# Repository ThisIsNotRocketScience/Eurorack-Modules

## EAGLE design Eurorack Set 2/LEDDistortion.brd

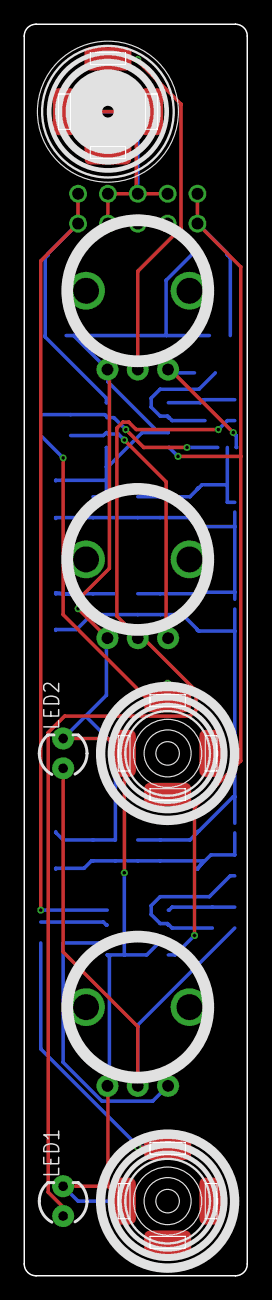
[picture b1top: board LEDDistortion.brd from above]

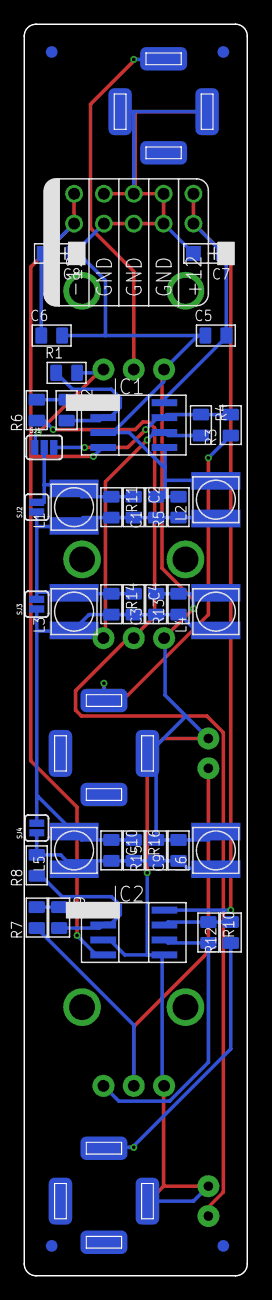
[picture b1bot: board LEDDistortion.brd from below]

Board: 2 copper layers, 19.0 x 106.5 mm, 52 parts (43 on the bottom side), 21 nets.

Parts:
C1, C2, C3, C4, C5, C6, C9, C10: 100n; C0805
C7, C8: 10u; AVX-A
GAIN1: 100k; OG-POTS_ALPS_POT_VERTICAL
IC1, IC2: TL072; SO08
L1, L2, L3, L4, L5, L6: TBD; L0420
LED1: REDBLUE; LED3MM
LED2: BLUERED; LED3MM
POST1, POST2: 100k; OG-POTS_ALPS_POT_VERTICAL
R1, R5, R8, R11, R13, R14, R15, R16: TBD; C0805
R2, R4, R9, R10: 100k; C0805
R3, R12: 100; C0805
R6, R7: 330; C0805
SJ1: SJ_3_PASTE1&2
SJ2, SJ3, SJ4: SOLDERJUMPERNC; SJ_2S
U$1: POWER_SIMPLE10; POWER_10
U$2: IN; 3.5MM-JACK-SWITCH-13MM-INPUT
U$3: OUT2; 3.5MM-JACK-SWITCH-13MM-OUTPUT
U$4: EURORACK_PCB4HP; EURORACK4HPPCB
U$5, U$7, U$8, U$9: FIDUCIAL; FIDUCIAL_1MM
U$6: OUT1; 3.5MM-JACK-SWITCH-13MM-OUTPUT

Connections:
GND: C1.2, C3.2, C5.1, C6.2, C7.-, C8.+, C9.2, GAIN1.P$1, IC1.3, IC1.5, IC2.3, IC2.5, L2.2, L4.2, L6.2, LED1.K, LED2.K, POST1.P$1, POST2.P$1, R5.2, R13.2, R15.2, U$1.3, U$1.4, U$1.5, U$1.6, U$1.7, U$1.8, U$2.RING@1, U$2.RING@2, U$2.SWITCH@1, U$2.SWITCH@2, U$3.RING@1, U$3.RING@2, U$6.RING@1, U$6.RING@2
unnamed: C2.1, L1.2, R11.1, SJ1.2, SJ2.2
unnamed: LED1.A, POST1.P$2, R6.1
unnamed: GAIN1.P$3, R1.2, SJ1.1
unnamed: IC1.6, POST1.P$3, R4.2
unnamed: R3.1, U$3.TIP@1, U$3.TIP@2
unnamed: GAIN1.P$2, U$2.TIP@1, U$2.TIP@2
unnamed: LED2.A, POST2.P$2, R7.1
unnamed: IC2.6, POST2.P$3, R10.2
unnamed: C1.1, C2.2, C4.1, L1.1, L2.1, L3.2, R5.1, R11.2, R14.1, SJ2.1, SJ3.2
unnamed: R12.1, U$6.TIP@1, U$6.TIP@2
unnamed: C9.1, C10.2, L5.1, L6.1, R8.2, R15.1, R16.2, SJ4.1
unnamed: C3.1, C4.2, C10.1, L3.1, L4.1, L5.2, R13.1, R14.2, R16.1, SJ3.1, SJ4.2
OP1NEG: IC1.2, R1.1, R2.2
OP1NEG1: IC2.2, R8.1, R9.2
OP1OUT: IC1.1, R2.1, R6.2
OP1OUT1: IC2.1, R7.2, R9.1
OP2OUT: IC1.7, R3.2, R4.1, SJ1.3
OP2OUT1: IC2.7, R10.1, R12.2
VNEG: C6.1, C8.-, IC1.4, IC2.4, U$1.1, U$1.2
VPOS: C5.2, C7.+, IC1.8, IC2.8, U$1.9, U$1.10

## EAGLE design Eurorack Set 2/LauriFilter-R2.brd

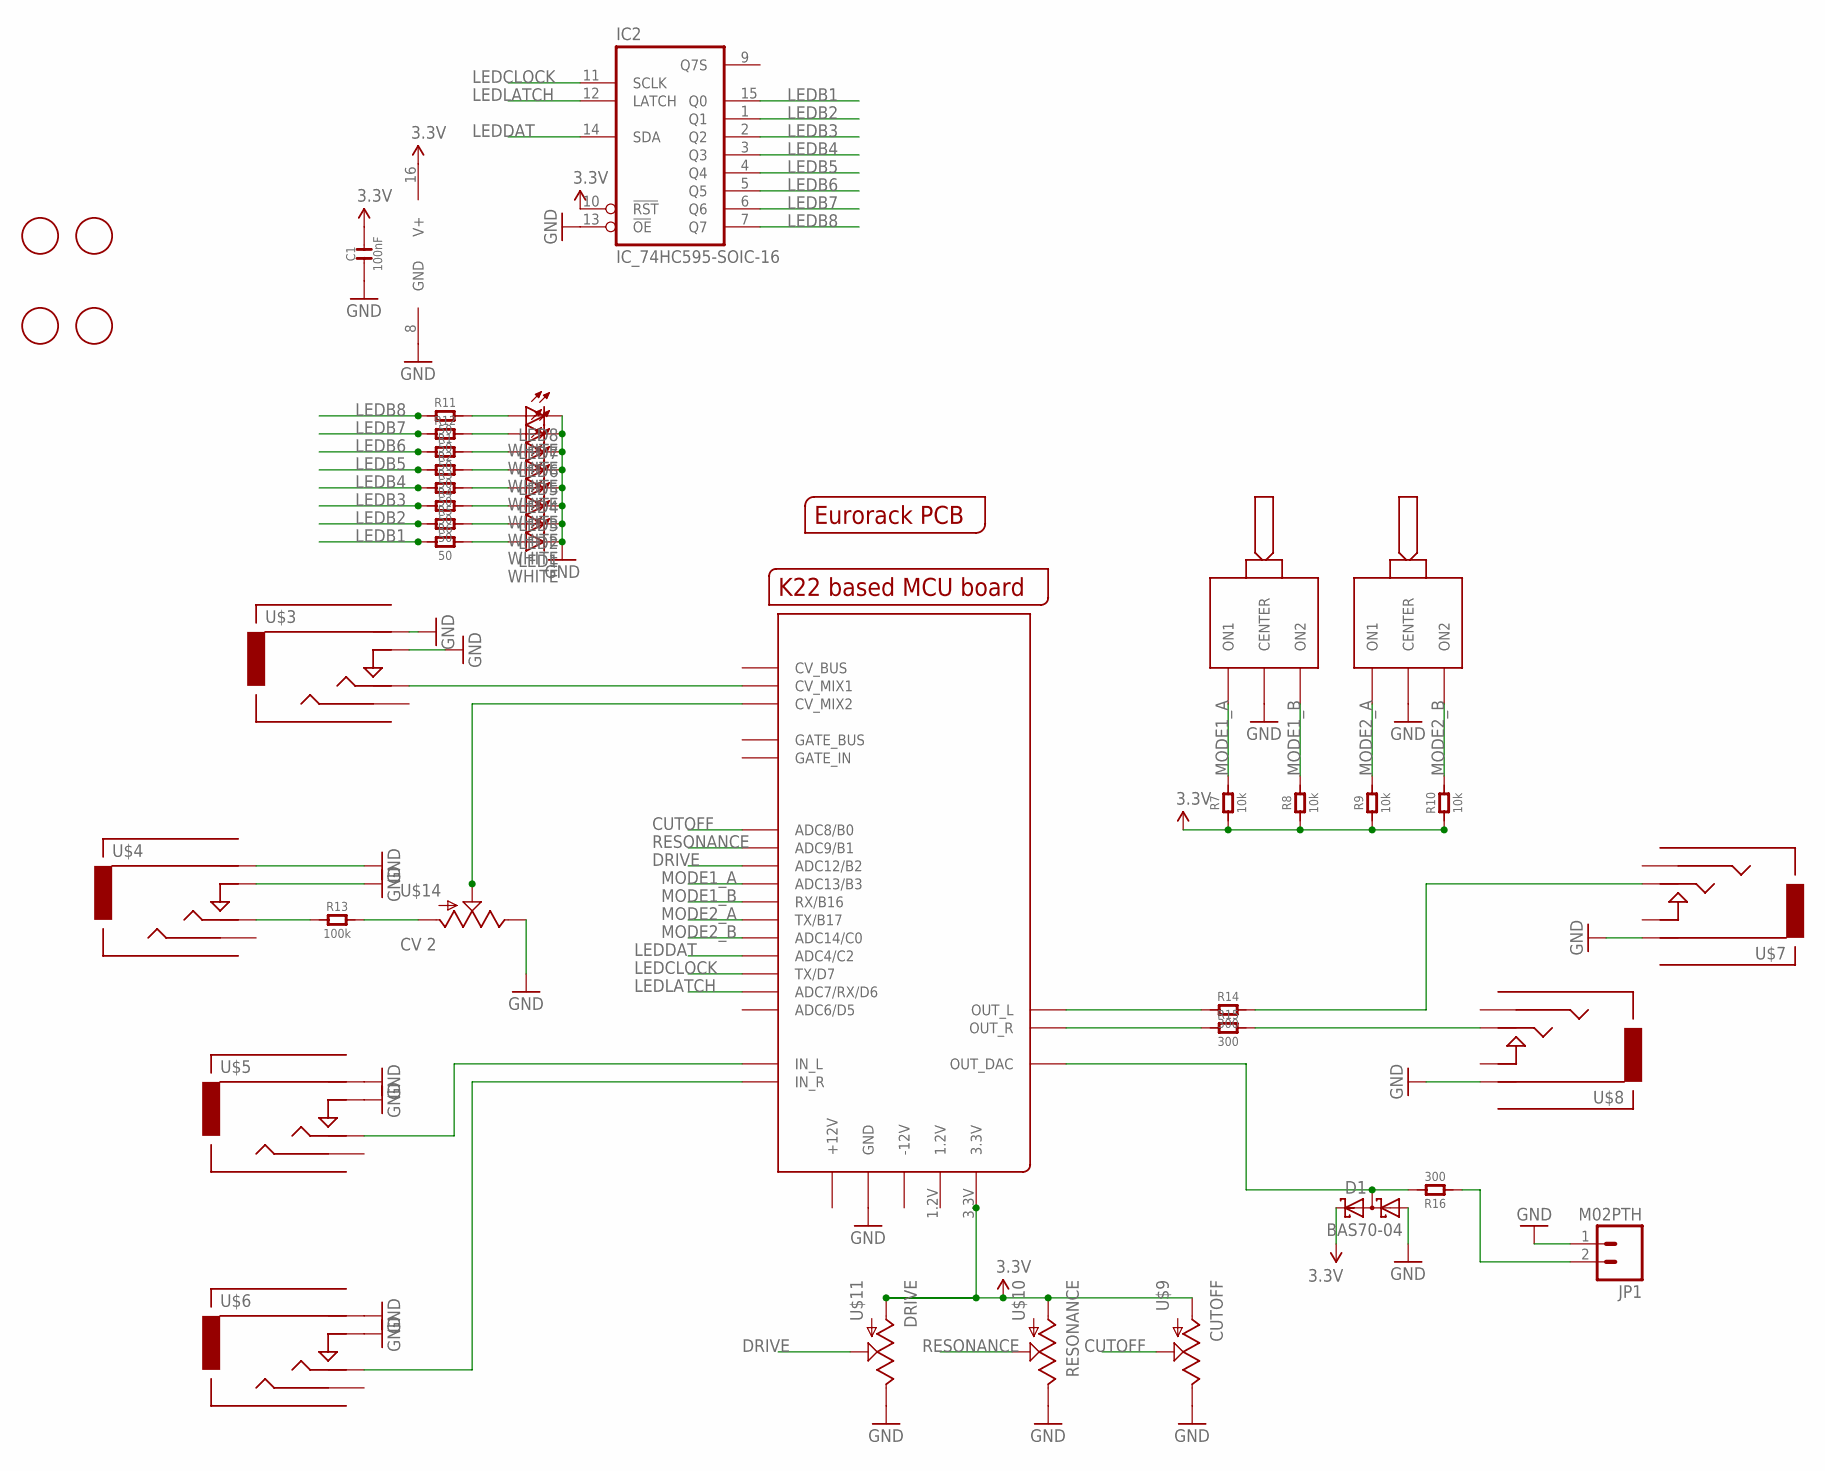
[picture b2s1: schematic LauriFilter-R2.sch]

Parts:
C1: 100nF; C0603
D1: BAS70-04; SOT23
IC2: IC_74HC595-SOIC-16; SOIC-16
JP1: M02PTH; 1X02
LED1, LED2, LED3, LED4, LED5, LED6, LED7, LED8: WHITE; LED3MM
R1, R2, R3, R4, R5, R6, R11, R12: 50; R0603
R7, R8, R9, R10: 10k; R0603
R13: 100k; R0603
R14, R15: 300; C0805
R16: 300; R0603
U$1: MCUBOARD; MCUBASEBOARD
U$2: EURORACK_PCB8HP; EURORACK8HPPCB
U$3: CV 1; 3.5MM-JACK-SWITCH-13MM-INPUT
U$4: CV 2; 3.5MM-JACK-SWITCH-13MM-INPUT
U$5: IN 1; 3.5MM-JACK-SWITCH-13MM-INPUT
U$6: IN 2; 3.5MM-JACK-SWITCH-13MM-INPUT
U$7: OUT 1; 3.5MM-JACK-SWITCH-13MM-OUTPUT
U$8: OUT 2; 3.5MM-JACK-SWITCH-13MM-OUTPUT
U$9: CUTOFF; OG-POTS_ALPS_POT_VERTICAL
U$10: RESONANCE; OG-POTS_ALPS_POT_VERTICAL
U$11: DRIVE; OG-POTS_ALPS_POT_VERTICAL
U$12, U$13: ONOFFON; MULTICOMP1MS-ONOFFON
U$14: CV 2; OG-POTS_ALPS_POT_VERTICAL
U$15, U$16, U$17, U$18: FIDUCIAL; FIDUCIAL_1MM

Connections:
3.3V: C1.2, D1.2 (C2), IC2.10 (!RST), IC2.16 (V+), R7.1, R8.1, R9.1, R10.1, U$1.3.3V, U$9.P$3 (A), U$10.P$3 (A), U$11.P$3 (A)
CUTOFF: U$1.ADC8 (ADC8/B0), U$9.P$2 (S)
DRIVE: U$1.ADC12 (ADC12/B2), U$11.P$2 (S)
GND: C1.1, D1.1 (A1), IC2.8 (GND), IC2.13 (!OE), JP1.1, LED1.K (C), LED2.K (C), LED3.K (C), LED4.K (C), LED5.K (C), LED6.K (C), LED7.K (C), LED8.K (C), U$1.GND@1 (GND), U$1.GND@2 (GND), U$1.GND@4 (GND), U$1.GND@5 (GND), U$1.GND@6 (GND), U$1.GND@7 (GND), U$1.GND@8 (GND), U$1.GND@9 (GND), U$1.GND_BUS (GND), U$3.RING@1 (RING), U$3.RING@2 (RING), U$3.SWITCH@1 (SWITCH), U$3.SWITCH@2 (SWITCH), U$4.RING@1 (RING), U$4.RING@2 (RING), U$4.SWITCH@1 (SWITCH), U$4.SWITCH@2 (SWITCH), U$5.RING@1 (RING), U$5.RING@2 (RING), U$5.SWITCH@1 (SWITCH), U$5.SWITCH@2 (SWITCH), U$6.RING@1 (RING), U$6.RING@2 (RING), U$6.SWITCH@1 (SWITCH), U$6.SWITCH@2 (SWITCH), U$7.RING@1 (RING), U$7.RING@2 (RING), U$8.RING@1 (RING), U$8.RING@2 (RING), U$9.P$1 (E), U$10.P$1 (E), U$11.P$1 (E), U$12.2 (CENTER), U$13.2 (CENTER), U$14.P$1 (E)
LEDB1: IC2.15 (Q0), R6.1
LEDB2: IC2.1 (Q1), R5.1
LEDB3: IC2.2 (Q2), R4.1
LEDB4: IC2.3 (Q3), R3.1
LEDB5: IC2.4 (Q4), R2.1
LEDB6: IC2.5 (Q5), R1.1
LEDB7: IC2.6 (Q6), R12.1
LEDB8: IC2.7 (Q7), R11.1
LEDCLOCK: IC2.11 (SCLK), U$1.TX/D7
LEDDAT: IC2.14 (SDA), U$1.ADC4 (ADC4/C2)
LEDLATCH: IC2.12 (LATCH), U$1.ADC7 (ADC7/RX/D6)
MODE1_A: R7.2, U$1.ADC13 (ADC13/B3), U$12.1 (ON1)
MODE1_B: R8.2, U$1.RX/B16, U$12.3 (ON2)
MODE2_A: R9.2, U$1.TX/B17, U$13.1 (ON1)
MODE2_B: R10.2, U$1.ADC14 (ADC14/C0), U$13.3 (ON2)
unnamed: U$1.IN_L, U$5.TIP@1 (TIP), U$5.TIP@2 (TIP)
unnamed: U$1.IN_R, U$6.TIP@1 (TIP), U$6.TIP@2 (TIP)
unnamed: U$1.CV_MIX1, U$3.TIP@1 (TIP), U$3.TIP@2 (TIP)
unnamed: U$1.CV_MIX2, U$14.P$2 (S)
unnamed: R14.2, U$7.TIP@1 (TIP), U$7.TIP@2 (TIP)
unnamed: R15.2, U$8.TIP@1 (TIP), U$8.TIP@2 (TIP)
unnamed: LED1.A, R6.2
unnamed: LED2.A, R5.2
unnamed: R14.1, U$1.OUT_L
unnamed: R15.1, U$1.OUT_R
unnamed: D1.3 (C1A2), R16.2, U$1.OUT_DAC
unnamed: LED3.A, R4.2
unnamed: LED4.A, R3.2
unnamed: LED5.A, R2.2
unnamed: LED6.A, R1.2
unnamed: LED7.A, R12.2
unnamed: LED8.A, R11.2
unnamed: JP1.2, R16.1
RESONANCE: U$1.ADC9 (ADC9/B1), U$10.P$2 (S)

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
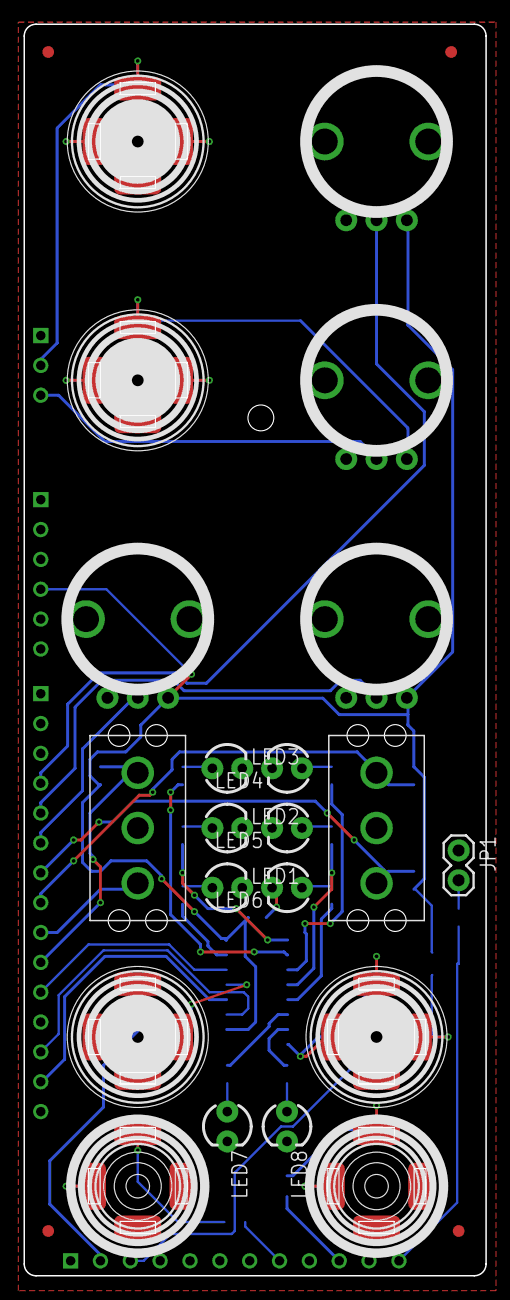
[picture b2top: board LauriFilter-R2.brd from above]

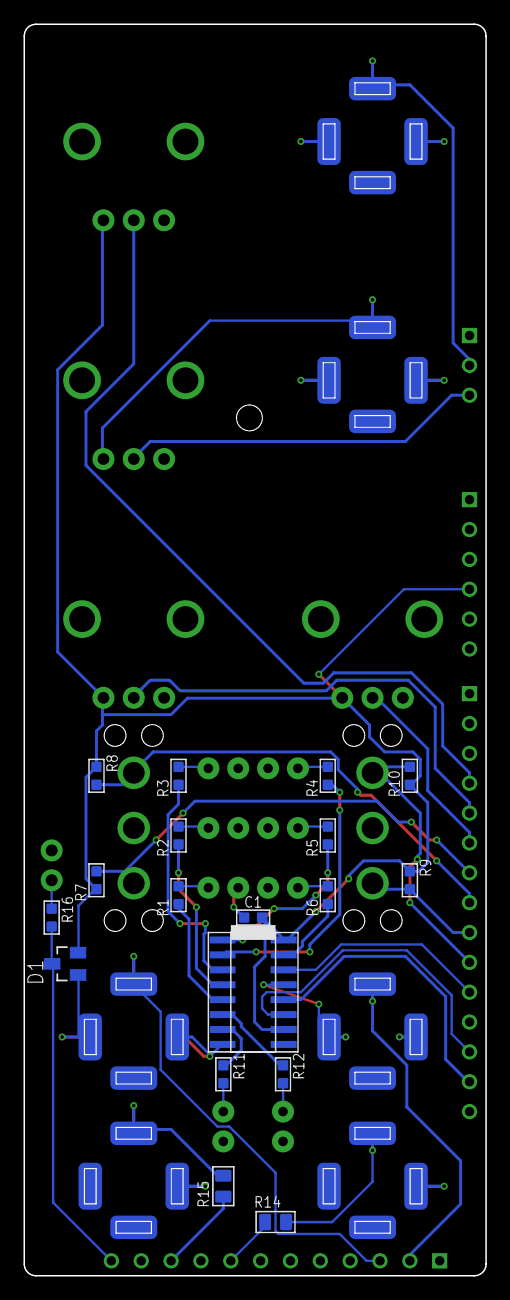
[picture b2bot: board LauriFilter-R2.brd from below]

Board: 2 copper layers, 39.3 x 106.5 mm, 45 parts (18 on the bottom side), 39 nets.

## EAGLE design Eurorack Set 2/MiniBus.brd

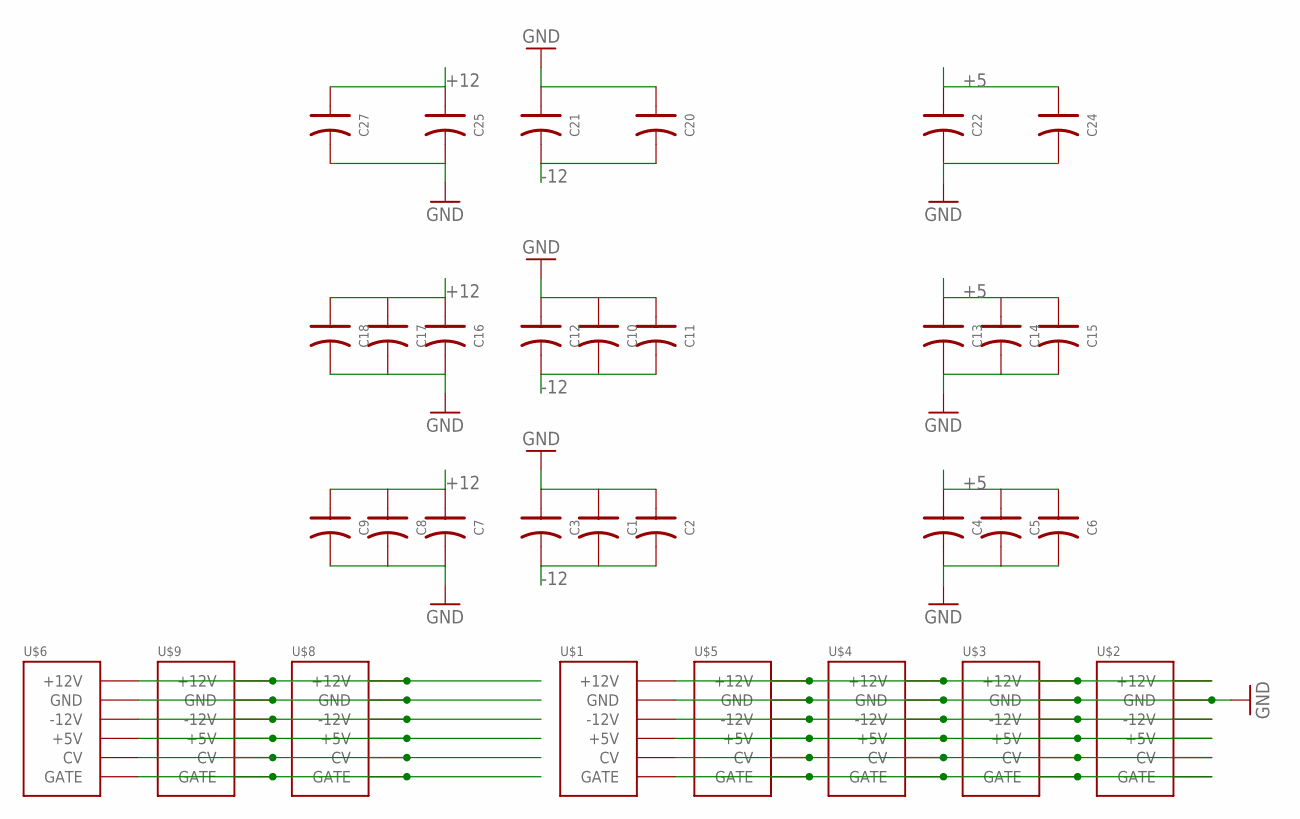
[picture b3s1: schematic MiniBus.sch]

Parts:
C1, C2, C3, C4, C5, C6, C7, C8, C9, C10, C11, C12, C13, C14, C15, C16, C17, C18, C20, C21, C22, C24, C25, C27: C-POLAR-A; AVX-A
U$1, U$2, U$3, U$4, U$5, U$6, U$8, U$9: POWER; POWER_16

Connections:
+5: C4.+ (1), C5.+ (1), C6.+ (1), C13.+ (1), C14.+ (1), C15.+ (1), C22.+ (1), C24.+ (1), U$1.11 (+5V), U$1.12 (+5V), U$2.11 (+5V), U$2.12 (+5V), U$3.11 (+5V), U$3.12 (+5V), U$4.11 (+5V), U$4.12 (+5V), U$5.11 (+5V), U$5.12 (+5V), U$6.11 (+5V), U$6.12 (+5V), U$8.11 (+5V), U$8.12 (+5V), U$9.11 (+5V), U$9.12 (+5V)
+12: C7.+ (1), C8.+ (1), C9.+ (1), C16.+ (1), C17.+ (1), C18.+ (1), C25.+ (1), C27.+ (1), U$1.9 (+12V), U$1.10 (+12V), U$2.9 (+12V), U$2.10 (+12V), U$3.9 (+12V), U$3.10 (+12V), U$4.9 (+12V), U$4.10 (+12V), U$5.9 (+12V), U$5.10 (+12V), U$6.9 (+12V), U$6.10 (+12V), U$8.9 (+12V), U$8.10 (+12V), U$9.9 (+12V), U$9.10 (+12V)
-12: C1.- (2), C2.- (2), C3.- (2), C10.- (2), C11.- (2), C12.- (2), C20.- (2), C21.- (2), U$1.1 (-12V), U$1.2 (-12V), U$2.1 (-12V), U$2.2 (-12V), U$3.1 (-12V), U$3.2 (-12V), U$4.1 (-12V), U$4.2 (-12V), U$5.1 (-12V), U$5.2 (-12V), U$6.1 (-12V), U$6.2 (-12V), U$8.1 (-12V), U$8.2 (-12V), U$9.1 (-12V), U$9.2 (-12V)
CV: U$1.13 (CV), U$1.14 (CV), U$2.13 (CV), U$2.14 (CV), U$3.13 (CV), U$3.14 (CV), U$4.13 (CV), U$4.14 (CV), U$5.13 (CV), U$5.14 (CV), U$6.13 (CV), U$6.14 (CV), U$8.13 (CV), U$8.14 (CV), U$9.13 (CV), U$9.14 (CV)
GATE: U$1.15 (GATE), U$1.16 (GATE), U$2.15 (GATE), U$2.16 (GATE), U$3.15 (GATE), U$3.16 (GATE), U$4.15 (GATE), U$4.16 (GATE), U$5.15 (GATE), U$5.16 (GATE), U$6.15 (GATE), U$6.16 (GATE), U$8.15 (GATE), U$8.16 (GATE), U$9.15 (GATE), U$9.16 (GATE)
GND: C1.+ (1), C2.+ (1), C3.+ (1), C4.- (2), C5.- (2), C6.- (2), C7.- (2), C8.- (2), C9.- (2), C10.+ (1), C11.+ (1), C12.+ (1), C13.- (2), C14.- (2), C15.- (2), C16.- (2), C17.- (2), C18.- (2), C20.+ (1), C21.+ (1), C22.- (2), C24.- (2), C25.- (2), C27.- (2), U$1.3 (GND), U$1.4 (GND), U$1.5 (GND), U$1.6 (GND), U$1.7 (GND), U$1.8 (GND), U$2.3 (GND), U$2.4 (GND), U$2.5 (GND), U$2.6 (GND), U$2.7 (GND), U$2.8 (GND), U$3.3 (GND), U$3.4 (GND), U$3.5 (GND), U$3.6 (GND), U$3.7 (GND), U$3.8 (GND), U$4.3 (GND), U$4.4 (GND), U$4.5 (GND), U$4.6 (GND), U$4.7 (GND), U$4.8 (GND), U$5.3 (GND), U$5.4 (GND), U$5.5 (GND), U$5.6 (GND), U$5.7 (GND), U$5.8 (GND), U$6.3 (GND), U$6.4 (GND), U$6.5 (GND), U$6.6 (GND), U$6.7 (GND), U$6.8 (GND), U$8.3 (GND), U$8.4 (GND), U$8.5 (GND), U$8.6 (GND), U$8.7 (GND), U$8.8 (GND), U$9.3 (GND), U$9.4 (GND), U$9.5 (GND), U$9.6 (GND), U$9.7 (GND), U$9.8 (GND)

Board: 2 copper layers, 32 parts (9 on the bottom side), 6 nets, no tracks yet.

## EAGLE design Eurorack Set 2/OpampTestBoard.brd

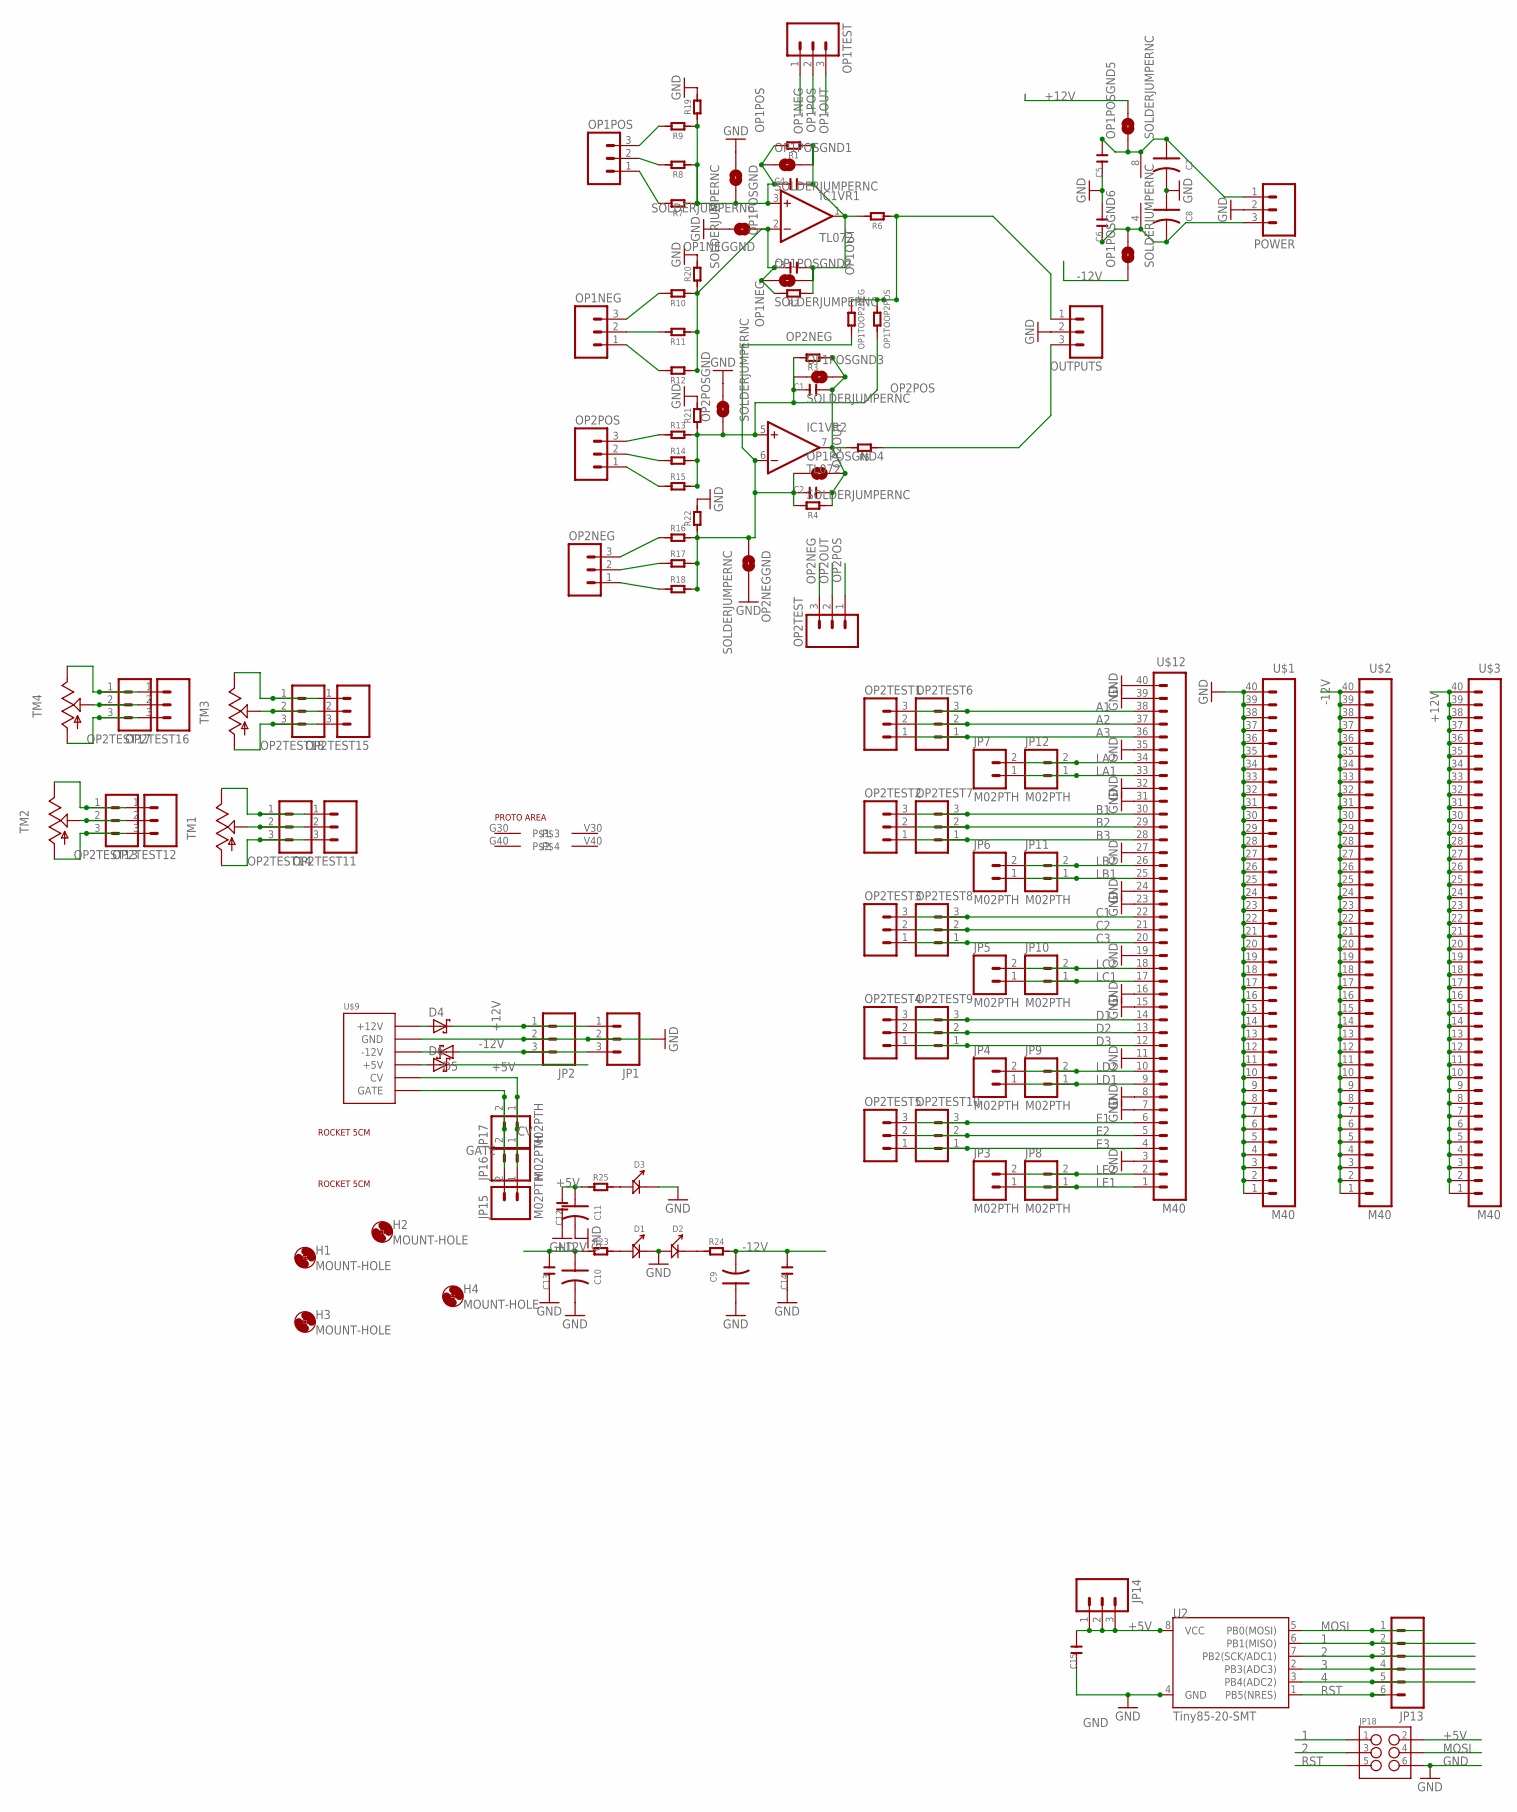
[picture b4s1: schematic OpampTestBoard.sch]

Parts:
C1, C2, C3, C4, C5, C6, C12, C13, C14: C-0805; C0805
C7, C8, C9, C10, C11: C-POLAR-A; AVX-A
C15: C-0603; C0603
D1, D2, D3: LED; LED0603
D4, D5, D6: SCHOTTKY-DIODEDO41; DO41-10
H1, H2, H3, H4: MOUNT-HOLE; 3.2-NOMARKINGS-SMALLSAFEZONE
IC1: TL072; SO08
JP1, JP2, JP14: M03PTH; 1X03
JP3, JP4, JP5, JP6, JP7, JP8, JP9, JP10, JP11, JP12, JP15, JP16, JP17: M02PTH; 1X02
JP13: M06SIP; 1X06
JP18: M03X2SMT; 2X3_SMT_POSTS
OP1NEG, OP1POS, OP1TEST, OP2NEG, OP2POS, OP2TEST, OP2TEST1, OP2TEST2, OP2TEST3, OP2TEST4, OP2TEST5, OP2TEST6, OP2TEST7, OP2TEST8, OP2TEST9, OP2TEST10, OP2TEST11, OP2TEST12, OP2TEST13, OP2TEST14, OP2TEST15, OP2TEST16, OP2TEST17, OP2TEST18: M03PTH; 1X03
OP1NEGGND, OP1POSGND, OP1POSGND1, OP1POSGND2, OP1POSGND3, OP1POSGND4, OP1POSGND5, OP1POSGND6, OP2NEGGND, OP2POSGND: SOLDERJUMPERNC; SJ_2S
OP1TOOP2NEG, OP1TOOP2POS: R-0603; R0603
OUTPUTS: M03PTH; 1X03
POWER: M03PTH; 1X03
R1, R2, R3, R4, R5, R6, R7, R8, R9, R10, R11, R12, R13, R14, R15, R16, R17, R18, R19, R20, R21, R22, R23, R24, R25: R-0603; R0603
TM1, TM2, TM3, TM4: TRIM; 6MM
U2: Tiny85-20-SMT; SO08-EIAJ
U$1, U$2, U$3, U$12: M40; 1X40
U$9: POWER; POWER_16
U$10, U$17: ROCKET-5CM
U$32: PROTOAREA; PROTO_10_24

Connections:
1: JP13.2, JP18.1, U2.6 (PB1(MISO))
2: JP13.3, JP18.3, U2.7 (PB2(SCK/ADC1))
3: JP13.4, U2.2 (PB3(ADC3))
4: JP13.5, U2.3 (PB4(ADC2))
+5V: C11.+ (1), C12.2, C15.2, D6.C, JP14.1, JP14.2, JP14.3, JP18.2, R25.1, U2.8 (VCC)
+12V: C10.+ (1), C13.2, D4.C, JP1.1, JP2.1, OP1POSGND5.2, R23.1, U$3.1, U$3.2, U$3.3, U$3.4, U$3.5, U$3.6, U$3.7, U$3.8, U$3.9, U$3.10, U$3.11, U$3.12, U$3.13, U$3.14, U$3.15, U$3.16, U$3.17, U$3.18, U$3.19, U$3.20, U$3.21, U$3.22, U$3.23, U$3.24, U$3.25, U$3.26, U$3.27, U$3.28, U$3.29, U$3.30, U$3.31, U$3.32, U$3.33, U$3.34, U$3.35, U$3.36, U$3.37, U$3.38, U$3.39, U$3.40
-12V: C9.- (2), C14.2, D5.A, JP1.3, JP2.3, OP1POSGND6.1, R24.2, U$2.1, U$2.2, U$2.3, U$2.4, U$2.5, U$2.6, U$2.7, U$2.8, U$2.9, U$2.10, U$2.11, U$2.12, U$2.13, U$2.14, U$2.15, U$2.16, U$2.17, U$2.18, U$2.19, U$2.20, U$2.21, U$2.22, U$2.23, U$2.24, U$2.25, U$2.26, U$2.27, U$2.28, U$2.29, U$2.30, U$2.31, U$2.32, U$2.33, U$2.34, U$2.35, U$2.36, U$2.37, U$2.38, U$2.39, U$2.40
A1: OP2TEST1.3, OP2TEST6.3, U$12.38
A2: OP2TEST1.2, OP2TEST6.2, U$12.37
A3: OP2TEST1.1, OP2TEST6.1, U$12.36
B1: OP2TEST2.3, OP2TEST7.3, U$12.30
B2: OP2TEST2.2, OP2TEST7.2, U$12.29
B3: OP2TEST2.1, OP2TEST7.1, U$12.28
C1: OP2TEST3.3, OP2TEST8.3, U$12.22
C2: OP2TEST3.2, OP2TEST8.2, U$12.21
C3: OP2TEST3.1, OP2TEST8.1, U$12.20
CV: JP15.1, JP16.1, JP17.1, U$9.13 (CV), U$9.14 (CV)
D1: OP2TEST4.3, OP2TEST9.3, U$12.14
D2: OP2TEST4.2, OP2TEST9.2, U$12.13
D3: OP2TEST4.1, OP2TEST9.1, U$12.12
E1: OP2TEST5.3, OP2TEST10.3, U$12.6
E2: OP2TEST5.2, OP2TEST10.2, U$12.5
E3: OP2TEST5.1, OP2TEST10.1, U$12.4
GATE: JP15.2, JP16.2, JP17.2, U$9.15 (GATE), U$9.16 (GATE)
GND: C5.1, C6.2, C7.- (2), C8.+ (1), C9.+ (1), C10.- (2), C11.- (2), C12.1, C13.1, C14.1, C15.1, D1.-, D2.+, D3.-, JP1.2, JP2.2, JP18.6, OP1NEGGND.2, OP1POSGND.1, OP2NEGGND.2, OP2POSGND.2, OUTPUTS.2, POWER.2, R19.2, R20.2, R21.2, R22.2, U2.4 (GND), U$1.1, U$1.2, U$1.3, U$1.4, U$1.5, U$1.6, U$1.7, U$1.8, U$1.9, U$1.10, U$1.11, U$1.12, U$1.13, U$1.14, U$1.15, U$1.16, U$1.17, U$1.18, U$1.19, U$1.20, U$1.21, U$1.22, U$1.23, U$1.24, U$1.25, U$1.26, U$1.27, U$1.28, U$1.29, U$1.30, U$1.31, U$1.32, U$1.33, U$1.34, U$1.35, U$1.36, U$1.37, U$1.38, U$1.39, U$1.40, U$9.3 (GND), U$9.4 (GND), U$9.5 (GND), U$9.6 (GND), U$9.7 (GND), U$9.8 (GND), U$12.3, U$12.7, U$12.8, U$12.11, U$12.15, U$12.16, U$12.19, U$12.23, U$12.24, U$12.27, U$12.31, U$12.32, U$12.35, U$12.39, U$12.40
LA1: JP7.1, JP12.1, U$12.33
LA2: JP7.2, JP12.2, U$12.34
LB1: JP6.1, JP11.1, U$12.25
LB2: JP6.2, JP11.2, U$12.26
LC1: JP5.1, JP10.1, U$12.17
LC2: JP5.2, JP10.2, U$12.18
LD1: JP4.1, JP9.1, U$12.9
LD2: JP4.2, JP9.2, U$12.10
LE1: JP3.1, JP8.1, U$12.1
LE2: JP3.2, JP8.2, U$12.2
MOSI: JP13.1, JP18.4, U2.5 (PB0(MOSI))
unnamed: OP1POS.3, R9.2
unnamed: OP1TOOP2NEG.1, OP1TOOP2POS.1, OUTPUTS.1, R6.1
unnamed: OP1POS.2, R8.2
unnamed: OUTPUTS.3, R5.1
unnamed: OP2TEST11.2, OP2TEST14.2, TM1.S
unnamed: OP2TEST12.2, OP2TEST13.2, TM2.S
unnamed: OP1POS.1, R7.2
unnamed: OP1NEG.3, R10.2
unnamed: OP1NEG.2, R11.2
unnamed: OP1NEG.1, R12.2
unnamed: OP2POS.3, R13.1
unnamed: OP2POS.2, R14.1
unnamed: OP2POS.1, R15.1
unnamed: OP2NEG.3, R16.1
unnamed: OP2NEG.2, R17.1
unnamed: OP2NEG.1, R18.1
unnamed: OP2TEST12.1, OP2TEST13.1, TM2.E
unnamed: D3.+, R25.2
unnamed: D1.+, R23.2
unnamed: D2.-, R24.1
unnamed: OP2TEST12.3, OP2TEST13.3, TM2.A
unnamed: OP2TEST11.1, OP2TEST14.1, TM1.E
unnamed: OP2TEST11.3, OP2TEST14.3, TM1.A
unnamed: OP2TEST15.2, OP2TEST18.2, TM3.S
unnamed: OP2TEST16.2, OP2TEST17.2, TM4.S
unnamed: OP2TEST16.1, OP2TEST17.1, TM4.E
unnamed: OP2TEST16.3, OP2TEST17.3, TM4.A
unnamed: OP2TEST15.1, OP2TEST18.1, TM3.E
unnamed: OP2TEST15.3, OP2TEST18.3, TM3.A
unnamed: D4.A, U$9.9 (+12V), U$9.10 (+12V)
unnamed: D5.C, U$9.1 (-12V), U$9.2 (-12V)
unnamed: D6.A, U$9.11 (+5V), U$9.12 (+5V)
OP1NEG: C3.1, IC1.2 (-IN), OP1NEGGND.1, OP1POSGND2.1, OP1TEST.1, R2.2, R10.1, R11.1, R12.1, R20.1
OP1OUT: C3.2, C4.2, IC1.1 (OUT), OP1POSGND1.2, OP1POSGND2.2, OP1TEST.3, R1.1, R2.1, R6.2
OP1POS: C4.1, IC1.3 (+IN), OP1POSGND.2, OP1POSGND1.1, OP1TEST.2, R1.2, R7.1, R8.1, R9.1, R19.1
OP2NEG: C2.1, IC1.6 (-IN), OP1POSGND4.1, OP1TOOP2NEG.2, OP2NEGGND.1, OP2TEST.3, R4.2, R16.2, R17.2, R18.2, R22.1
OP2OUT: C1.2, C2.2, IC1.7 (OUT), OP1POSGND3.2, OP1POSGND4.2, OP2TEST.2, R3.1, R4.1, R5.2
OP2POS: C1.1, IC1.5 (+IN), OP1POSGND3.1, OP1TOOP2POS.2, OP2POSGND.1, OP2TEST.1, R3.2, R13.2, R14.2, R15.2, R21.1
RST: JP13.6, JP18.5, U2.1 (PB5(NRES))
VNEG: C6.1, C8.- (2), IC1.4 (V-), OP1POSGND6.2, POWER.3
VPOS: C5.2, C7.+ (1), IC1.8 (V+), OP1POSGND5.1, POWER.1

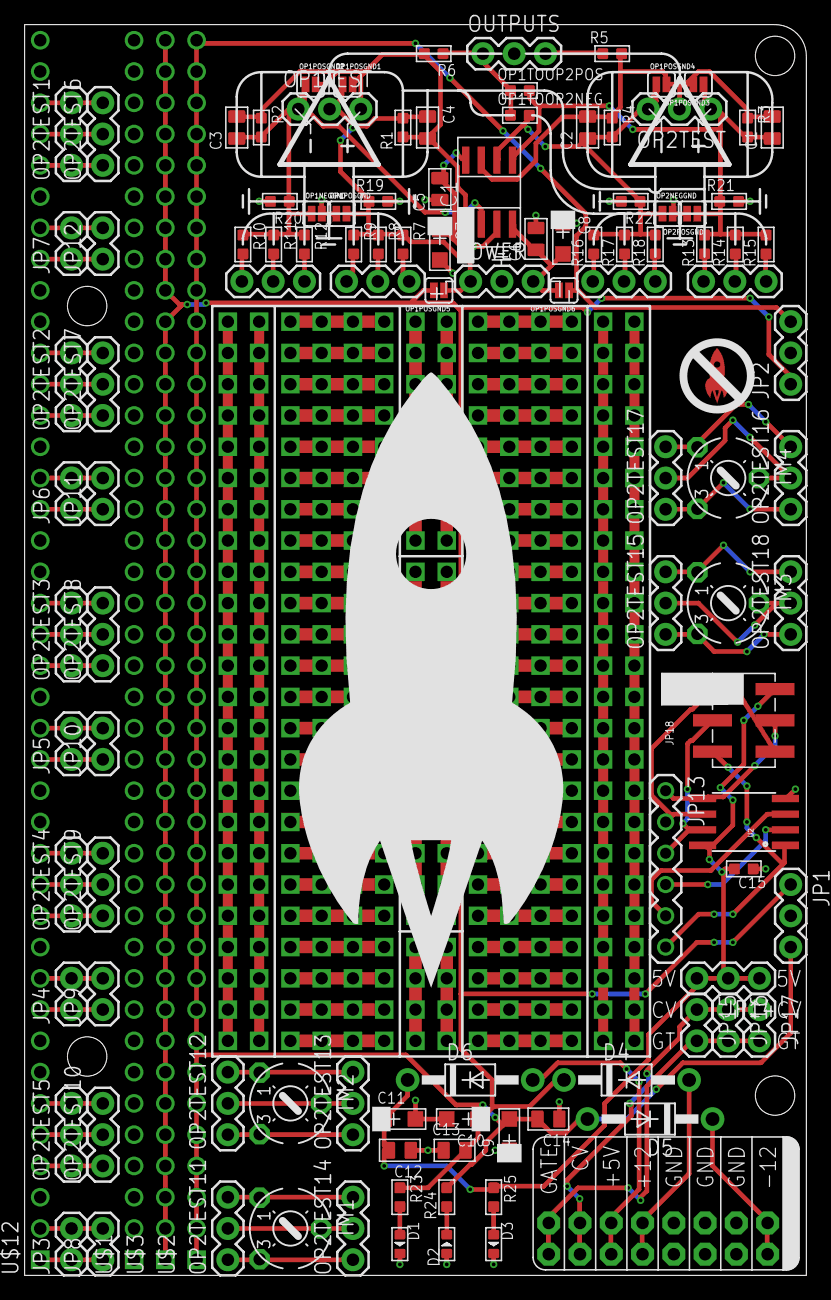
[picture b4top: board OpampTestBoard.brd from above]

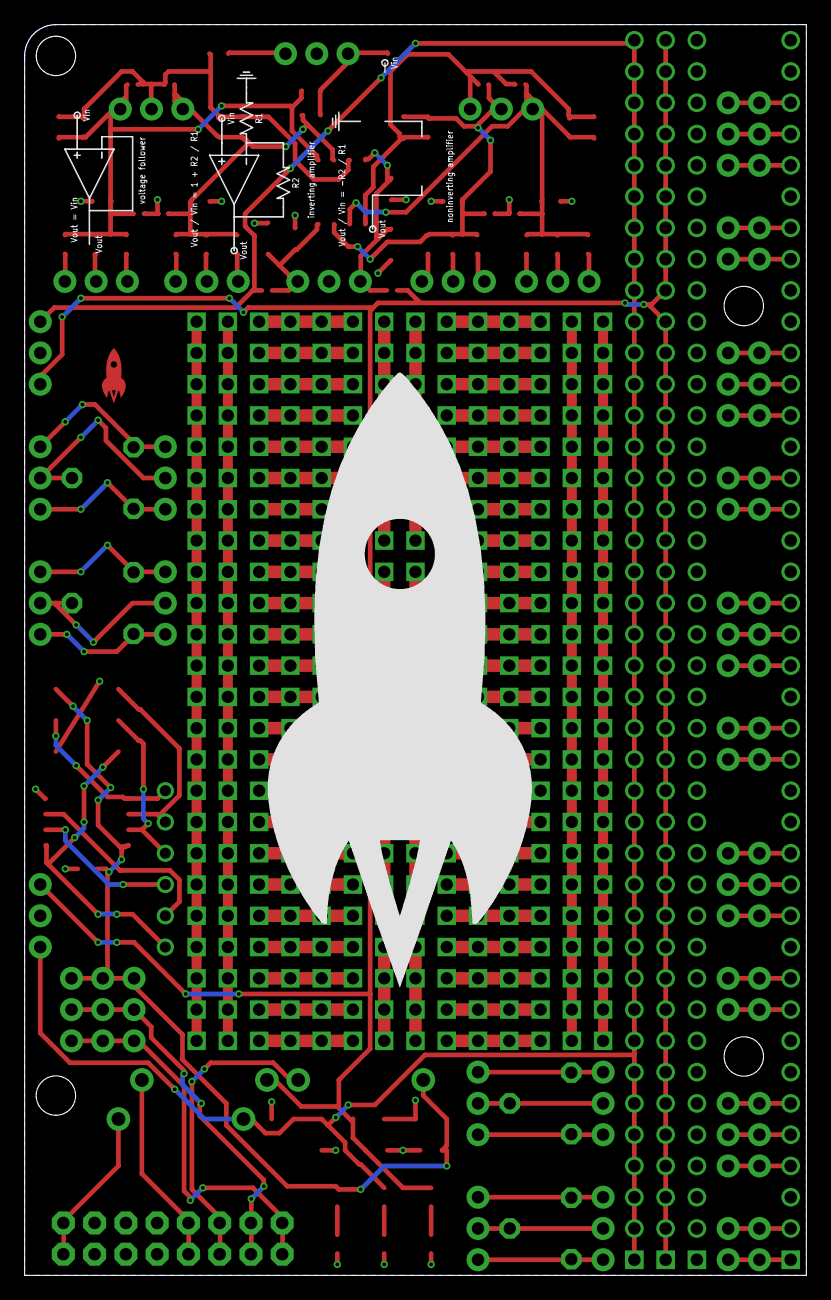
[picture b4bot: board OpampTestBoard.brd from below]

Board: 2 copper layers, 63.5 x 101.6 mm, 125 parts (5 on the bottom side), 77 nets.

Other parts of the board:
U$4, U$7: SYMBOLSOPAMP; SYMB_OPAMP
U$5: R2; RESISTOR
U$6: R1; RESISTOR
U$8: SMALLROCKET

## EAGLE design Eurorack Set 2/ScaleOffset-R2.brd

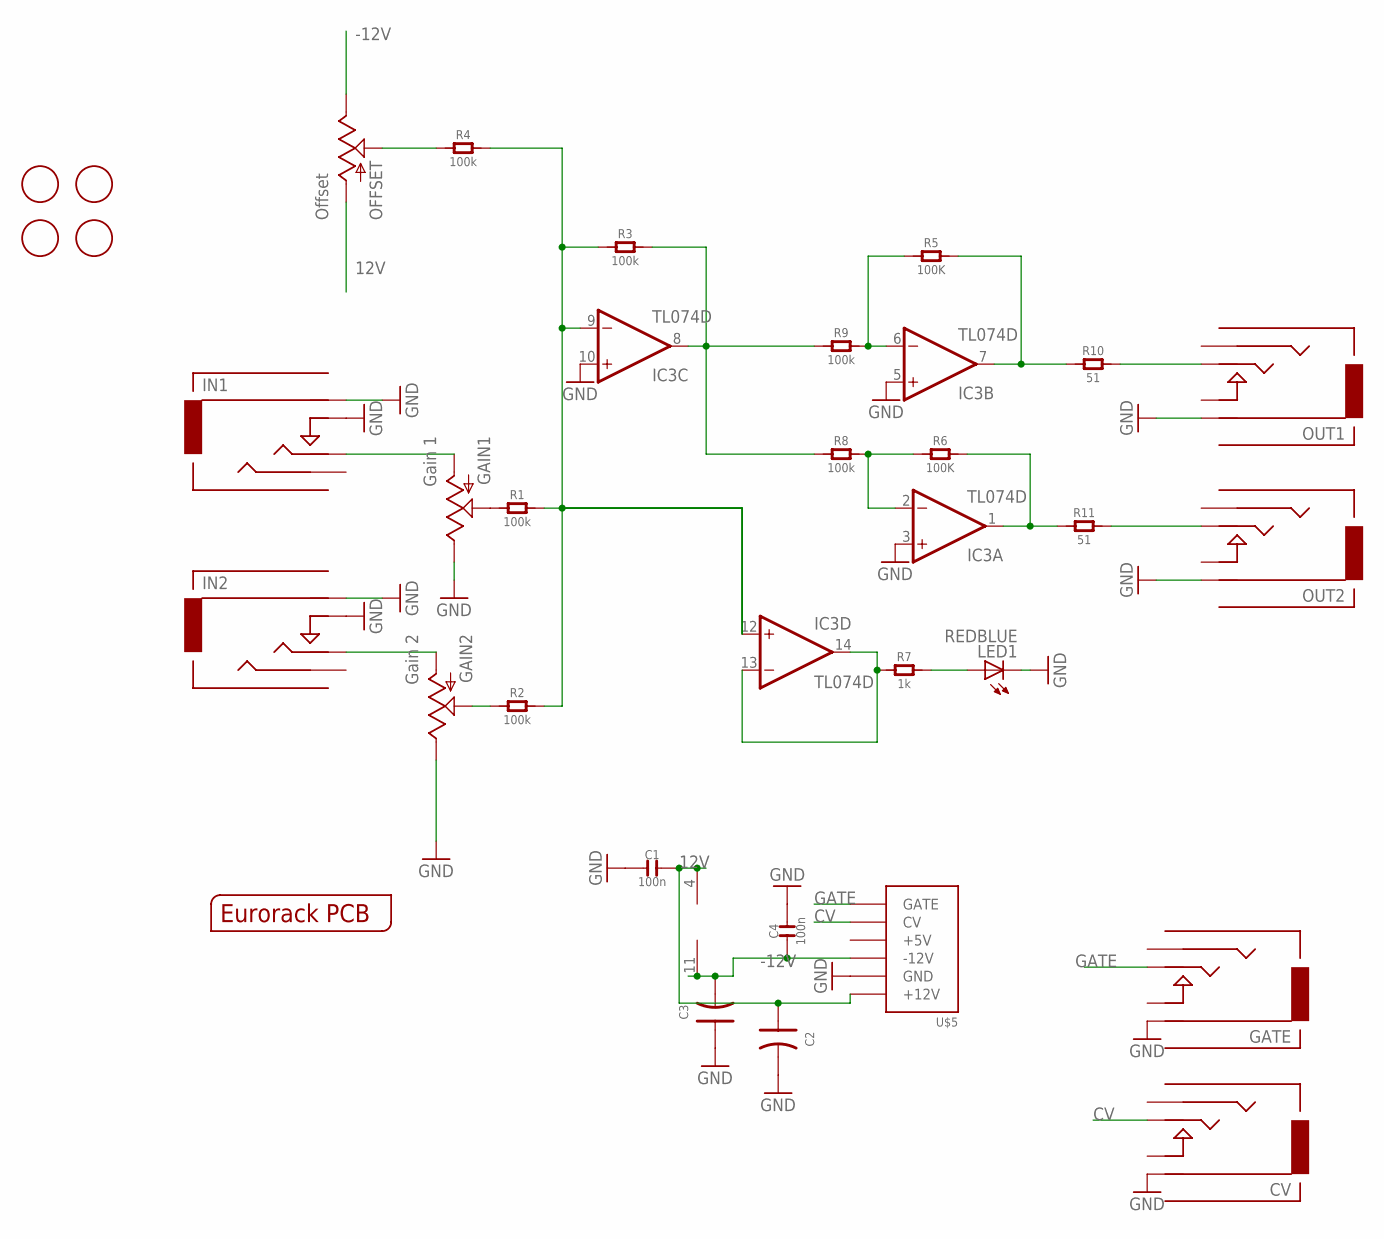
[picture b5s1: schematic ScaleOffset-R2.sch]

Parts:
C1, C4: 100n; C0603
C2, C3: C-POLAR-A; AVX-A
CV: CV; 3.5MM-JACK-SWITCH-13MM-OUTPUT
GAIN1: Gain 1; OG-POTS_ALPS_POT_VERTICAL
GAIN2: Gain 2; OG-POTS_ALPS_POT_VERTICAL
GATE: GATE; 3.5MM-JACK-SWITCH-13MM-OUTPUT
IC3: TL074D; SO14
IN1: Input 1; 3.5MM-JACK-SWITCH-13MM-INPUT
IN2: Input 2; 3.5MM-JACK-SWITCH-13MM-INPUT
LED1: REDBLUE; LED3MM
OFFSET: Offset; OG-POTS_ALPS_POT_VERTICAL
OUT1: 2; 3.5MM-JACK-SWITCH-13MM-OUTPUT
OUT2: 1; 3.5MM-JACK-SWITCH-13MM-OUTPUT
R1, R2, R3, R4, R8, R9: 100k; R0603
R5, R6: 100K; R0603
R7: 1k; R0603
R10, R11: 51; C0805
U$1, U$2, U$3, U$4: FIDUCIAL; FIDUCIAL_1MM
U$5: POWER; POWER_16
U$12: EURORACK_PCB6HP; EURORACK6HPPCB

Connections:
12V: C1.2, C2.+ (1), IC3.4 (V+), OFFSET.P$3 (A), U$5.9 (+12V), U$5.10 (+12V)
-12V: C3.- (2), C4.1, IC3.11 (V-), OFFSET.P$1 (E), U$5.1 (-12V), U$5.2 (-12V)
CV: CV.TIP@1 (TIP), CV.TIP@2 (TIP), U$5.13 (CV), U$5.14 (CV)
FBOUT1: IC3.7 (OUT), R5.2, R10.1
FBOUT2: IC3.1 (OUT), R6.2, R11.1
GATE: GATE.TIP@1 (TIP), GATE.TIP@2 (TIP), U$5.15 (GATE), U$5.16 (GATE)
GND: C1.1, C2.- (2), C3.+ (1), C4.2, CV.RING@1 (RING), CV.RING@2 (RING), GAIN1.P$1 (E), GAIN2.P$1 (E), GATE.RING@1 (RING), GATE.RING@2 (RING), IC3.3 (+IN), IC3.5 (+IN), IC3.10 (+IN), IN1.RING@1 (RING), IN1.RING@2 (RING), IN1.SWITCH@1 (SWITCH), IN1.SWITCH@2 (SWITCH), IN2.RING@1 (RING), IN2.RING@2 (RING), IN2.SWITCH@1 (SWITCH), IN2.SWITCH@2 (SWITCH), LED1.K (C), OUT1.RING@1 (RING), OUT1.RING@2 (RING), OUT2.RING@1 (RING), OUT2.RING@2 (RING), U$5.3 (GND), U$5.4 (GND), U$5.5 (GND), U$5.6 (GND), U$5.7 (GND), U$5.8 (GND)
unnamed: IC3.6 (-IN), R5.1, R9.2
unnamed: LED1.A, R7.2
unnamed: GAIN2.P$3 (A), IN2.TIP@1 (TIP), IN2.TIP@2 (TIP)
unnamed: GAIN1.P$3 (A), IN1.TIP@1 (TIP), IN1.TIP@2 (TIP)
unnamed: GAIN1.P$2 (S), R1.1
unnamed: GAIN2.P$2 (S), R2.1
unnamed: IC3.8 (OUT), R3.2, R8.1, R9.1
unnamed: IC3.13 (-IN), IC3.14 (OUT), R7.1
unnamed: IC3.2 (-IN), R6.1, R8.2
OFFSET: OFFSET.P$2 (S), R4.1
OUT1: OUT1.TIP@1 (TIP), OUT1.TIP@2 (TIP), R10.2
OUT2: OUT2.TIP@1 (TIP), OUT2.TIP@2 (TIP), R11.2
SUMMING: IC3.9 (-IN), IC3.12 (+IN), R1.2, R2.2, R3.1, R4.2

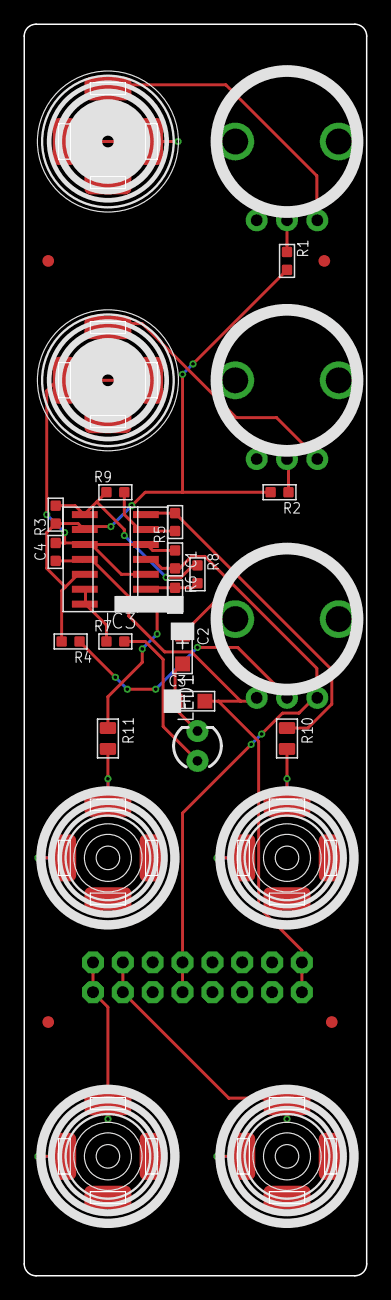
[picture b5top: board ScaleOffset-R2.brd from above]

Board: 2 copper layers, 29.1 x 106.5 mm, 32 parts (1 on the bottom side), 20 nets.

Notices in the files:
parts and their libraries:
SparkFun-LED: Licensing: CC v3.0 Share-Alike You are welcome to use this library for commercial purposes.
